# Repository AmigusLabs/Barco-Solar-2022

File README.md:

# Barco-Solar-2022

Hemos creado de nuevo (<a href="https://www.amiguslabs.org/portfolio_page/barco-solar/" target="_blank">Barco 2018</a> -  <a href="https://www.amiguslabs.org/portfolio_page/amigus-labs-barco-solar19/" target="_blank">Barco 2019</a>) un barco impreso en 3d para participar en la <a href="http://regatasolar.org" target="_blank">Regata Solar de Marine Instruments</a>. Esta vez un trimaran de unos 9Kg de peso y un volumen total de 29 litros.

Se ha diseñado integramente en Cinema 4D, con subdivisión de superficies (curvas Nurbs).

Una vez modelado, se han dividio en 32 piezas para imprimir, secciones de hasta 250x250x200mm y exportado a STL. Para optimizar la impresión intentamos que cada sección no tardase más de 10 horas en imprimirse, para intentar imprimir por el dia y dormir por la noche :P El software de slicer usado es el Simplify3D y la impresora una Ender 5 Plus.

Evitanto el uso de soportes a la hora de imprimir se han hecho algunas secciones que finalmente se pegan para poder imprimir sobre el lado más plano y evitar luego el postprocesado.

Una vez impresas las piezas, y para facilitar la rigidez a la hora de pegarlas, se han hecho unas secciones en cada pieza para pegar y encajar unos pequeños tubos impresos de unos 10x10x50mm. Se ha pegado todas las partes con pegamento para modelismo comprado en bazar chino, tarda unas 4 horas en secar y quedan las piezas muy rígidas. En las zonas que por sharping de las piezas hizo falta se relleno de masilla para carrocerías de Ceys. 

Para darle el acabado final, una vez pegadas todas las piezas, se ha aplicado imprimación de color blanco y posteriormente una mano de Epoxi. En el montaje, en las zonas más irregulares se le aplicó un poco de lijado.

Para encajar las partes de electrónica al barco, así como el soporte de la placa solar, se han usado unos insertos de M5 y M3 aplicados con solador, que evitan el uso de tuercas y hacen que las zonas de enrosque queden bien sujetas.

Para las tapas se ha usado goma Eva cortado en laser para hacer las zonas de unión impermeables (gracias a <a href="https://fablableon.org" target="_blank">Fab Lab León</a> y <a href="https://www.esne.es" target="_blank">ESNE</a> por facilitarnos el corte en sus máquinas).

## Electrónica

Hemos intentado hacer una nueva PCB partiendo de un Attiny1614. Se ha diseñado la pcb en KiCAD, integrando un sensor INA219 para la optimización del voltaje y potencia de la placa solar basandonos en la propuesta de <a href="https://github.com/aindustriosa/Solar_MPPT_board" target="_blank">A Industriosa</a> del año 2019.

Con los limites de potencia y memoria del Attiny1614, hemos implementado el uso del sensor así como un divisor de voltaje para leerlo via VREF. Los mensajes enviados desd eel mando RC al receptor, son procesados por el microcontrolador y en caso de exigirle una velocidad mayor al 30% entra en modo automático, y prioriza el rendimiento que este generando la placa solar en ese momento a optener la velocidad optima sin permitir la caida de potencia por un exceso del rendimiento de la placa solar.

## Materiales

8x PETG 1Kg Blanco 1.75mm (<a href="https://www.amazon.es/dp/B08C4YP5RS/ref=twister_B08HSFRV2M?_encoding=UTF8&th=1" target="_blank">Amazon</a>)

1x Smartfil FLEX - Filamento Flexible (<a href="https://www.smartmaterials3d.com/flex-filamento#/1-tamano-s_330g/26-diametro-175_mm/29-color-sapphire" target="_blank">Smart Materials 3D</a>)
  
3x Tubos cuadrados de 10x10x500mm - <a href="https://www.clipcarbono.com/es/home/947-tubo-exterior-cuadrado-10x10-mm-interior-cuadrado-8x8-mm-de-fibra-de-carbono-longitud-1000-mm.html" target="_blank">Tubo cuadrado, exterior (10x10 mm.) - interior (8x8 mm.) de fibra de carbono - Longitud 1000 mm.</a> Cortesía de <a href="https://www.clipcarbono.com" target="_blank">ClipCarbono</a>

1x Castropox 4307/1209 Resina Epoxi de usos generales (<a href="https://www.castrocompositesshop.com/es/resinas/1099-resina-epoxi-castropox-43071209.html" target="_blank">Castro Composites</a>)

1x Masilla Carrocerias Ceys (<a href="https://www.amazon.es/Desconocido-M59016-Adhesivo-masilla-carrocerias/dp/B00ITVXML6" target="_blank">Amazon</a>)

3x Imprimación Plástico (<a href="https://www.amazon.es/MTN-IMPRIMACIÓN-PLÁSTICOS-400-ML/dp/B00WG2K6W2/ref=sr_1_15?__mk_es_ES=ÅMÅŽÕÑ&crid=2E2QZXNCDXAI6&keywords=imprimacion&qid=1655512005&sprefix=imprimacion%2Caps%2C124&sr=8-15" target="_blank">Amazon</a>)

1x soporte helice y timón (<a href="https://es.aliexpress.com/item/32901476708.html" target="_blank">Aliexpress</a>)

100x Inserto roscado M3 (<a href="https://www.amazon.es/gp/product/B08BCRZZS3/ref=ppx_yo_dt_b_asin_title_o00_s00?ie=UTF8&th=1" target="_blank">Amazon</a>)

6x Inserto roscado M5 (<a href="https://www.amazon.es/gp/product/B07YSVXWS8/ref=ppx_yo_dt_b_asin_title_o00_s00?ie=UTF8&th=1" target="_blank">Amazon</a>)

1x Acoplamiento Motor 4x5mm (<a href="https://www.amazon.es/gp/product/B09LV3KD4H/ref=ppx_yo_dt_b_asin_title_o05_s00?ie=UTF8&th=1" target="_blank">Amazon</a>)

1x Motor NTM Prop Drive 28-30 800KV (<a href="https://hobbyking.com/es_es/propdrive-v2-2830-800kv-brushless-outrunner-motor.html" target="_blank">Hobbyking</a>)

1x Turnigy Multistart 20A V2 ESC (<a href="https://hobbyking.com/es_es/turnigy-multistar-20a-v2-esc-with-blheli-and-4a-lbec-2-6s.html" target="_blank">Hobbyking</a>)

## Enlaces

- <a href="http://regatasolar.org" target="_blank">Regata Solar de Marine Instruments</a>
- <a href="https://www.amiguslabs.org" target="_blank">Amigus Labs</a>
- <a href="https://www.clipcarbono.com" target="_blank">ClipCarbono</a>
- <a href="http://aindustriosa.org" target="_blank">A Industriosa</a>
- <a href="https://fablableon.org" target="_blank">Fab Lab León</a>
- <a href="https://www.esne.es" target="_blank">ESNE</a>

Proxecto patrocinado por Xunta de Galicia e Amtega Axencia para a Modernización Tecnolóxica

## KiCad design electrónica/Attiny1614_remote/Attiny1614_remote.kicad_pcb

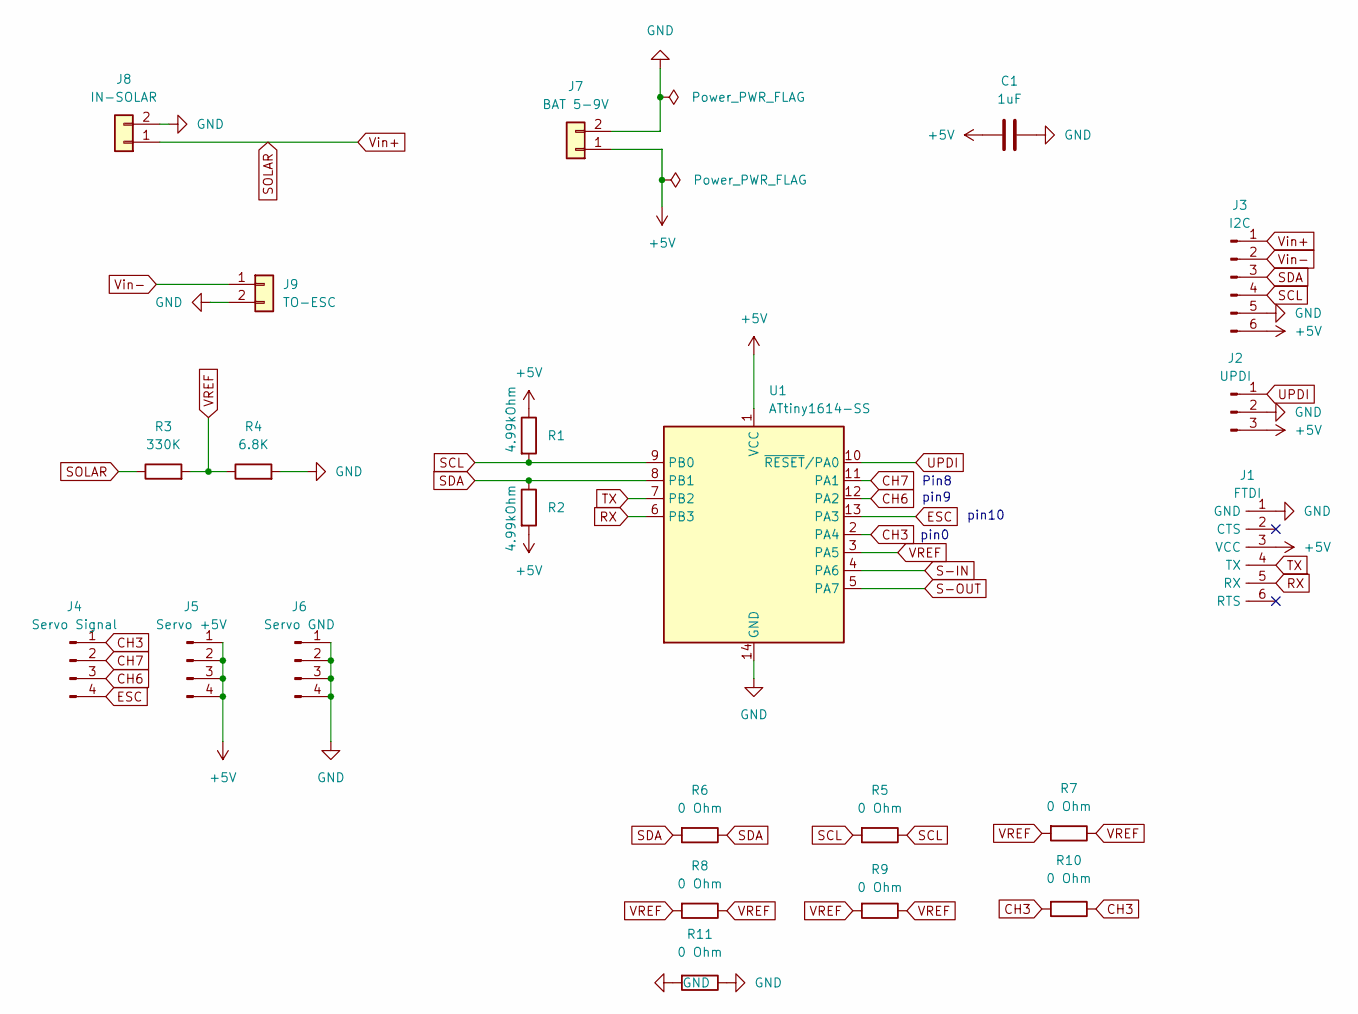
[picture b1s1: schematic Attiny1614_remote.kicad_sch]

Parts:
C1: 1uF; C_1206
J1: FTDI; PinHeader_1x06_P2.54mm_Vertical_THT_D1mm
J2: UPDI; PinHeader_1x03_P2.54mm_Vertical_THT_D1mm
J3: I2C; PinHeader_1x06_P2.54mm_Vertical_THT_D1mm
J4: Servo Signal; PinHeader_1x04_P2.54mm_Vertical_THT_D1mm
J5: Servo +5V; PinHeader_1x04_P2.54mm_Vertical_THT_D1mm
J6: Servo GND; PinHeader_1x04_P2.54mm_Vertical_THT_D1mm
J7: BAT 5-9V; JST_XH_B2B-XH-A_1x02_P2.50mm_Vertical
J8: IN-SOLAR; AMASS_XT60-F_1x02_P7.20mm_Vertical
J9: TO-ESC; AMASS_XT60-F_1x02_P7.20mm_Vertical
R1, R2: 4.99kOhm; R_1206
R3: 330K; R_1206
R4: 6.8K; R_1206
R5, R6, R7, R8, R9, R10, R11: 0 Ohm; R_1206
U1: ATtiny1614-SS; SOIC-14_3.9x8.7mm_P1.27mm

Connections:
+5V: C1.1, J1.3 (VCC), J2.3, J3.6, J5.1, J5.2, J5.3, J5.4, J7.1, R1.1, R2.2, U1.1 (VCC)
CH3: J4.1, R10.1, R10.2, U1.2 (PA4)
CH6: J4.3, U1.12 (PA2)
CH7: J4.2, U1.11 (PA1)
ESC: J4.4, U1.13 (PA3)
GND: C1.2, J1.1 (GND), J2.2, J3.5, J6.1, J6.2, J6.3, J6.4, J7.2, J8.2, J9.2, R4.2, R11.1, R11.2, U1.14 (GND)
RX: J1.5 (RX), U1.6 (PB3)
S-IN: U1.4 (PA6)
S-OUT: U1.5 (PA7)
SCL: J3.4, R1.2, R5.1, R5.2, U1.9 (PB0)
SDA: J3.3, R2.1, R6.1, R6.2, U1.8 (PB1)
SOLAR: J3.1, J8.1, R3.1
TX: J1.4 (TX), U1.7 (PB2)
UPDI: J2.1, U1.10 (~RESET/PA0)
VREF: R3.2, R4.1, R7.1, R7.2, R8.1, R8.2, R9.1, R9.2, U1.3 (PA5)
Vin-: J3.2, J9.1

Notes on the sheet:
Pin8
pin10
pin0
pin9

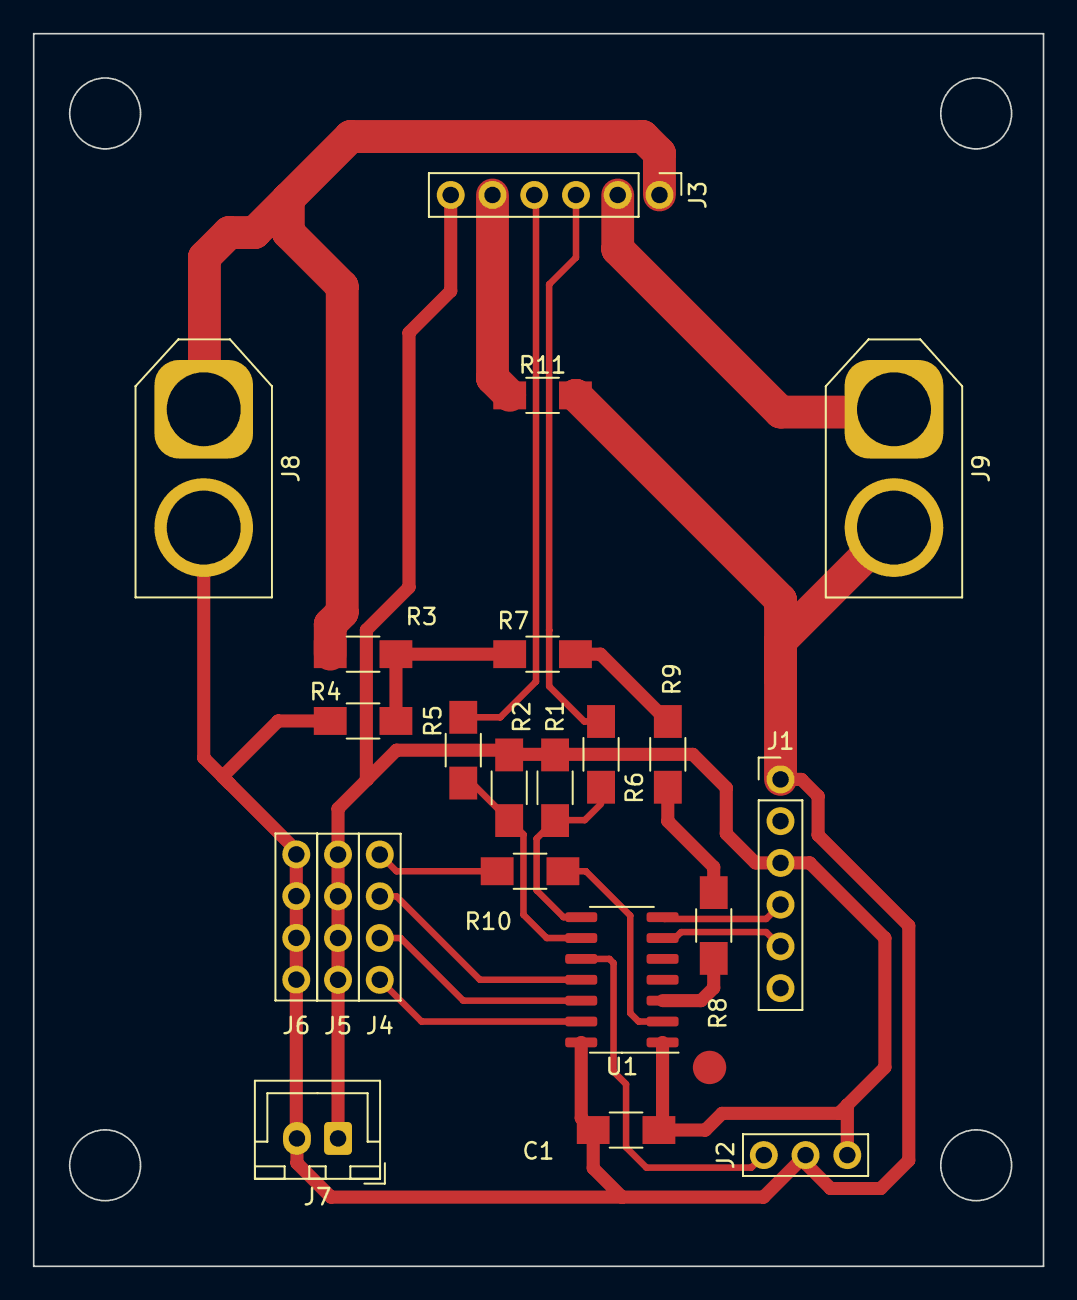
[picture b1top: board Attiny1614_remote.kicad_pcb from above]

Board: 2 copper layers, 61.4 x 75.0 mm, 22 parts (0 on the bottom side), 14 nets.

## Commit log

2022-06-17 /Corte_laser
2022-06-17 Ficheros
2022-06-17 ficheros Centro Barco
    Limite 25Mb, se han comprimido algunos ficheros como .zip
2022-06-17 Contenido
2022-06-17 imagenes
2022-06-17 Intersecciones
2022-06-17 up render
2022-06-17 partes
2022-06-18 Nurbs
2022-06-18 Create Electrónica
2022-06-18 ficheros nuevos
2022-06-18 KiCad
2022-06-18 Kicad images
2022-06-21 update code
2022-06-21 update STL
    Nuevas piezas soporte bandera TPU y soporte barco
2022-06-21 update soft
